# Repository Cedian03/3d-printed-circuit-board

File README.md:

# 3D Printed Circuit Board

Work in progress 3D printable keyboard PCB. Traces are formed with copper tape guided by raised 3D printed tracks.

## Board properties

- Board thickness is set at `PCB Editor->Board setup->Physical Stackup->Dielectric 1->Thickness`
- Trace height is set at `PCB Editor->Board setup->Physical Stackup->F.Cu/B.Cu->Thickness`

Or they can be edited in CAD after exporting.

## Recommended export settings

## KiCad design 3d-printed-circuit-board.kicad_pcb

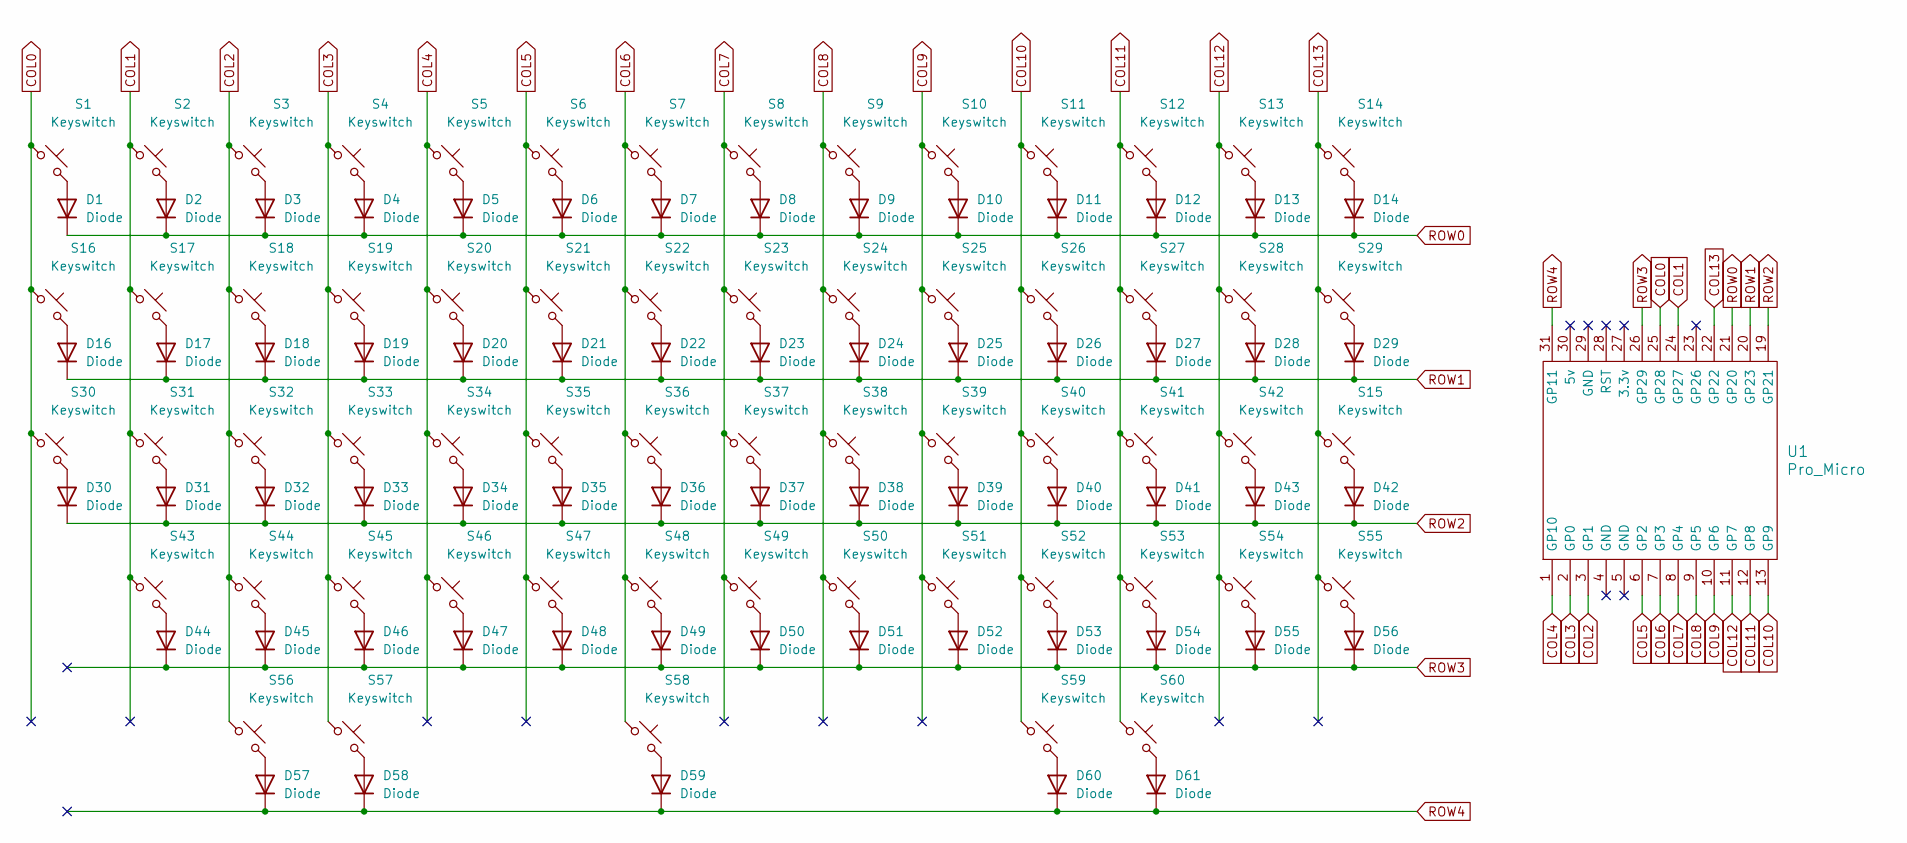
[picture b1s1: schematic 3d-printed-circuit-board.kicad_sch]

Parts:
D1, D2, D3, D4, D5, D6, D7, D8, D9, D10, D11, D12, D13, D14, D16, D17, D18, D19, D20, D21, D22, D23, D24, D25, D26, D27, D28, D29, D30, D31, D32, D33, D34, D35, D36, D37, D38, D39, D40, D41, D42, D43, D44, D45, D46, D47, D48, D49, D50, D51, D52, D53, D54, D55, D56, D57, D58, D59, D60, D61: Diode; Diode_DO-35
S1, S2, S3, S4, S5, S6, S7, S8, S9, S10, S11, S12, S13, S14, S15, S16, S17, S18, S19, S20, S21, S22, S23, S24, S25, S26, S27, S28, S29, S30, S31, S32, S33, S34, S35, S36, S37, S38, S39, S40, S41, S42, S43, S44, S45, S46, S47, S48, S49, S50, S51, S52, S53, S54, S55, S56, S57, S58, S59, S60: Keyswitch; MX_PCB_1.00u
U1: Pro_Micro; RP2040_Pro_Micro

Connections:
COL0: S1.1, S16.1, S30.1, U1.25 (GP28)
COL1: S2.1, S17.1, S31.1, S43.1, U1.24 (GP27)
COL2: S3.1, S18.1, S32.1, S44.1, S56.1, U1.3 (GP1)
COL3: S4.1, S19.1, S33.1, S45.1, S57.1, U1.2 (GP0)
COL4: S5.1, S20.1, S34.1, S46.1, U1.1 (GP10)
COL5: S6.1, S21.1, S35.1, S47.1, U1.6 (GP2)
COL6: S7.1, S22.1, S36.1, S48.1, S58.1, U1.7 (GP3)
COL7: S8.1, S23.1, S37.1, S49.1, U1.8 (GP4)
COL8: S9.1, S24.1, S38.1, S50.1, U1.9 (GP5)
COL9: S10.1, S25.1, S39.1, S51.1, U1.10 (GP6)
COL10: S11.1, S26.1, S40.1, S52.1, S59.1, U1.13 (GP9)
COL11: S12.1, S27.1, S41.1, S53.1, S60.1, U1.12 (GP8)
COL12: S13.1, S28.1, S42.1, S54.1, U1.11 (GP7)
COL13: S14.1, S15.1, S29.1, S55.1, U1.22 (GP22)
unnamed: D1.2 (A), S1.2
unnamed: D2.2 (A), S2.2
unnamed: D3.2 (A), S3.2
unnamed: D4.2 (A), S4.2
unnamed: D5.2 (A), S5.2
unnamed: D6.2 (A), S6.2
unnamed: D7.2 (A), S7.2
unnamed: D8.2 (A), S8.2
unnamed: D9.2 (A), S9.2
unnamed: D10.2 (A), S10.2
unnamed: D11.2 (A), S11.2
unnamed: D12.2 (A), S12.2
unnamed: D13.2 (A), S13.2
unnamed: D14.2 (A), S14.2
unnamed: D16.2 (A), S16.2
unnamed: D17.2 (A), S17.2
unnamed: D18.2 (A), S18.2
unnamed: D19.2 (A), S19.2
unnamed: D20.2 (A), S20.2
unnamed: D21.2 (A), S21.2
unnamed: D22.2 (A), S22.2
unnamed: D23.2 (A), S23.2
unnamed: D24.2 (A), S24.2
unnamed: D25.2 (A), S25.2
unnamed: D26.2 (A), S26.2
unnamed: D27.2 (A), S27.2
unnamed: D28.2 (A), S28.2
unnamed: D29.2 (A), S29.2
unnamed: D30.2 (A), S30.2
unnamed: D31.2 (A), S31.2
unnamed: D32.2 (A), S32.2
unnamed: D33.2 (A), S33.2
unnamed: D34.2 (A), S34.2
unnamed: D35.2 (A), S35.2
unnamed: D36.2 (A), S36.2
unnamed: D37.2 (A), S37.2
unnamed: D38.2 (A), S38.2
unnamed: D39.2 (A), S39.2
unnamed: D40.2 (A), S40.2
unnamed: D41.2 (A), S41.2
unnamed: D42.2 (A), S15.2
unnamed: D43.2 (A), S42.2
unnamed: D44.2 (A), S43.2
unnamed: D45.2 (A), S44.2
unnamed: D46.2 (A), S45.2
unnamed: D47.2 (A), S46.2
unnamed: D48.2 (A), S47.2
unnamed: D49.2 (A), S48.2
unnamed: D50.2 (A), S49.2
unnamed: D51.2 (A), S50.2
unnamed: D52.2 (A), S51.2
unnamed: D53.2 (A), S52.2
unnamed: D54.2 (A), S53.2
unnamed: D55.2 (A), S54.2
unnamed: D56.2 (A), S55.2
unnamed: D57.2 (A), S56.2
unnamed: D58.2 (A), S57.2
unnamed: D59.2 (A), S58.2
unnamed: D60.2 (A), S59.2
unnamed: D61.2 (A), S60.2
ROW0: D1.1 (K), D2.1 (K), D3.1 (K), D4.1 (K), D5.1 (K), D6.1 (K), D7.1 (K), D8.1 (K), D9.1 (K), D10.1 (K), D11.1 (K), D12.1 (K), D13.1 (K), D14.1 (K), U1.21 (GP20)
ROW1: D16.1 (K), D17.1 (K), D18.1 (K), D19.1 (K), D20.1 (K), D21.1 (K), D22.1 (K), D23.1 (K), D24.1 (K), D25.1 (K), D26.1 (K), D27.1 (K), D28.1 (K), D29.1 (K), U1.20 (GP23)
ROW2: D30.1 (K), D31.1 (K), D32.1 (K), D33.1 (K), D34.1 (K), D35.1 (K), D36.1 (K), D37.1 (K), D38.1 (K), D39.1 (K), D40.1 (K), D41.1 (K), D42.1 (K), D43.1 (K), U1.19 (GP21)
ROW3: D44.1 (K), D45.1 (K), D46.1 (K), D47.1 (K), D48.1 (K), D49.1 (K), D50.1 (K), D51.1 (K), D52.1 (K), D53.1 (K), D54.1 (K), D55.1 (K), D56.1 (K), U1.26 (GP29)
ROW4: D57.1 (K), D58.1 (K), D59.1 (K), D60.1 (K), D61.1 (K), U1.31 (GP11)

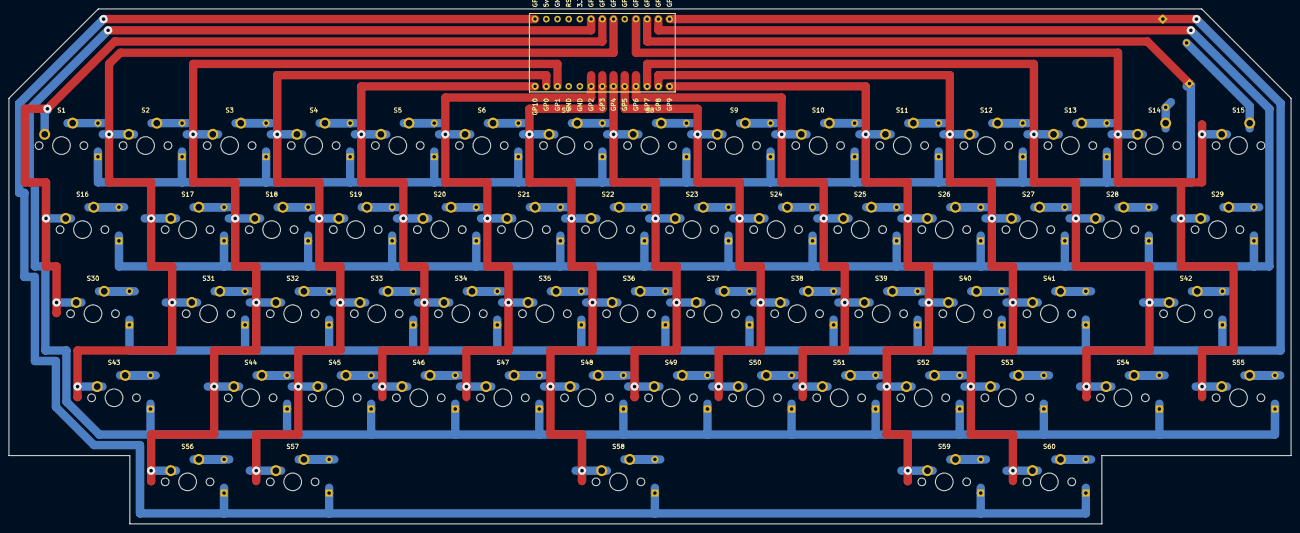
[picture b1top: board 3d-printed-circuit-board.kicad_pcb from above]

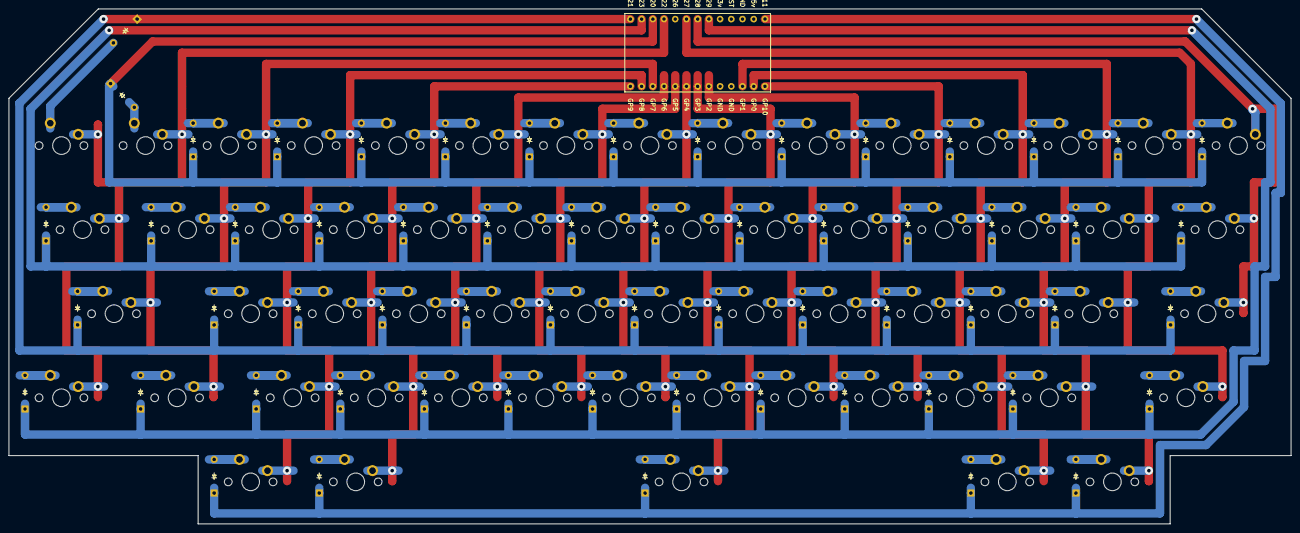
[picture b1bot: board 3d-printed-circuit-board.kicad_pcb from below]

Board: 2 copper layers, 290.5 x 116.7 mm, 121 parts (60 on the bottom side), 79 nets.

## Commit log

2026-03-23 Add column stagger
2026-03-23 Use copper layer thickness to raise traces
2026-03-23 Add basic README
2026-03-23 Fix typos
2026-03-23 Add MCU footprint
2026-03-24 Revise routing to reduce solder points
2026-03-27 Add image of v0.3 prototype
2026-04-02 Route full hhkb layout
